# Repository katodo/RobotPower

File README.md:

# RobotPower
A Rosserial + **Arduino DUE** based work for Robot's battery and power managment

##Clone and install from source Rosserial 
See reference documentation of [Rosserial](http://wiki.ros.org/rosserial_arduino/Tutorials/Arduino%20IDE%20Setup)

##Add u8glib library to Arduino's GUI
(u8glib)[https://github.com/olikraus/u8glib] library is needed, you can add (Arduino ZIP version)[https://github.com/olikraus/U8glib_Arduino/releases/latest] directly from **Arduino GUI -> Sketch -> Include Library -> Add .ZIP Library**

##Clone this code and load it in an Arduino DUE board.

##Run RosCore.

```
you$ roscore
... logging to /home/you/.ros/log/d6f526e8-644b-11e6-8eba-00044b26fb48/roslaunch-plutarco-3242.log
Checking log directory for disk usage. This may take awhile.
Press Ctrl-C to interrupt
Done checking log file disk usage. Usage is <1GB.

started roslaunch server http://plutarco.local:56239/
ros_comm version 1.11.20

SUMMARY
========

PARAMETERS
 * /rosdistro: indigo
 * /rosversion: 1.11.20

NODES

auto-starting new master
process[master]: started with pid [3253]
ROS_MASTER_URI=http://plutarco.local:11311/

setting /run_id to d6f526e8-644b-11e6-8eba-00044b26fb48
process[rosout-1]: started with pid [3266]
started core service [/rosout]
```
pay attention to ROS version: *rosdistro: indigo* 

##Run serial_node.py 
This is an output example of output of my *rosrun rosserial_python serial_node.py /dev/ttyACM0* command
```
you$ rosrun rosserial_python serial_node.py /dev/ttyACM0
[INFO] [WallTime: 1471330769.673572] ROS Serial Python Node
[INFO] [WallTime: 1471330769.679982] Connecting to /dev/ttyACM0 at 57600 baud
[ERROR] [WallTime: 1471330786.785870] Unable to sync with device; possible link problem or link software version mismatch such as hydro rosserial_python with groovy Arduino
[INFO] [WallTime: 1471330786.966402] Note: publish buffer size is 512 bytes
[INFO] [WallTime: 1471330786.966842] Setup publisher on BatteryState [sensor_msgs/BatteryState]
[INFO] [WallTime: 1471330786.971024] Setup publisher on adc [rosserial_arduino/Adc]
[INFO] [WallTime: 1471330786.975058] Setup publisher on chatter [std_msgs/String]
```

#Usage Example
There is 3 type of published messages in the first ( test ) release of this code
```
you$ rostopic list 
/BatteryState
/adc
/chatter
```

In a console I can see published message content with *rostopic echo* command

### Chatter message
```
you$ rostopic echo /chatter 
data: hello world!
---
data: hello world!
---
```

### ADC message
```
your$ rostopic echo /adc     
adc0: 0
adc1: 0
adc2: 0
adc3: 0
adc4: 0
adc5: 46509
```

### BatteryState message
```
you$ rostopic echo /BatteryState 
header: 
  seq: 996
  stamp: 
    secs: 0
    nsecs:         0
  frame_id: ''
voltage: 23.2210006714
current: -2.90000009537
charge: 0.240999996662
capacity: 3.59999990463
design_capacity: 5.0
percentage: 0.930000007153
power_supply_status: 2
power_supply_health: 1
power_supply_technology: 2
present: True
cell_voltage: [3.628000020980835, 3.628999948501587, 3.515000104904175, 4.0]
location: robot
serial_number: 123456790
---

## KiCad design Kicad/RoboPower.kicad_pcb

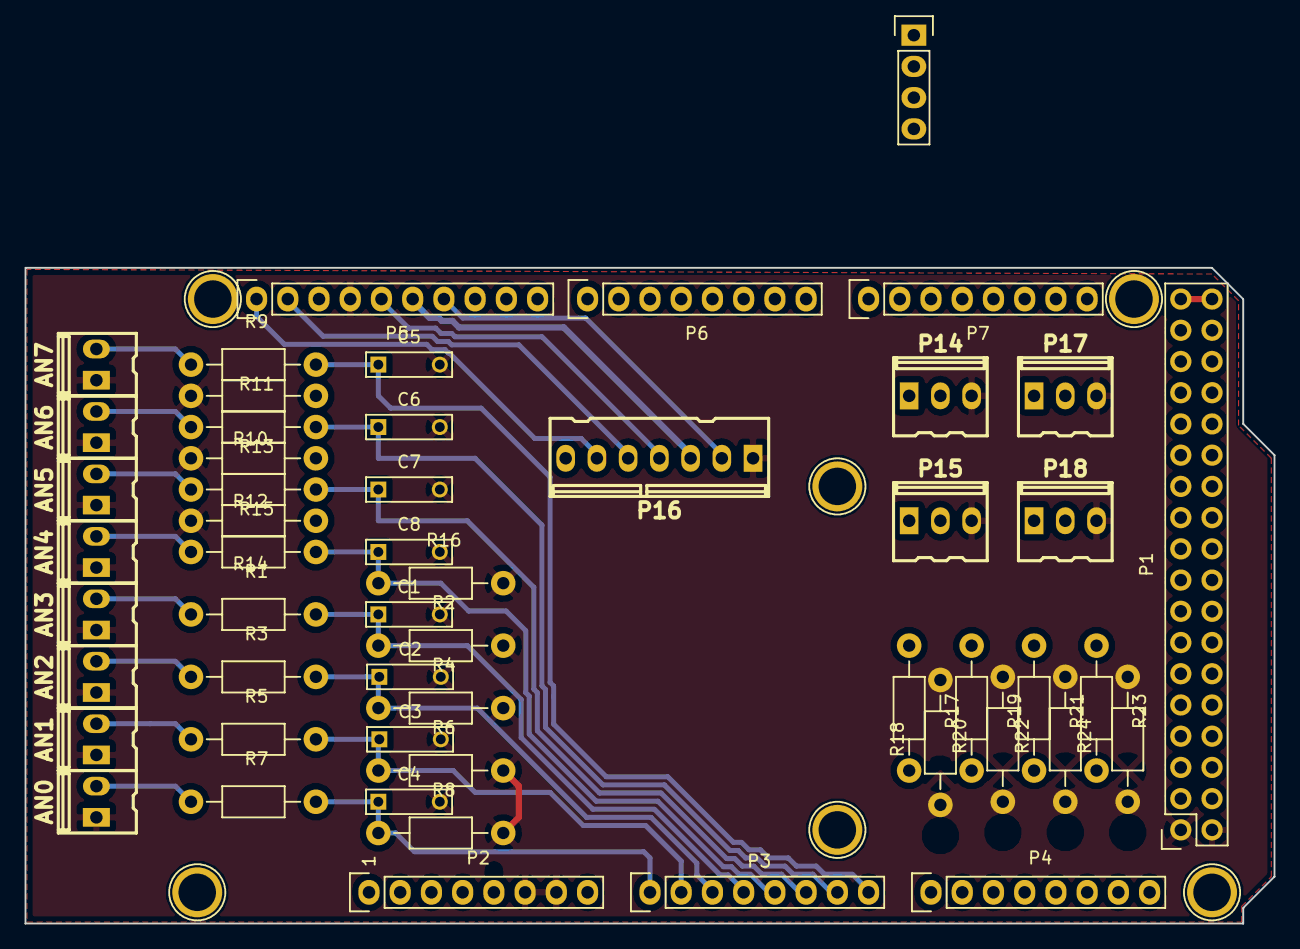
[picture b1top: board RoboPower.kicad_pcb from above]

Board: 2 copper layers, 101.6 x 53.3 mm, 59 parts (0 on the bottom side), 34 nets.

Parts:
AN0, AN1, AN2, AN3, AN4, AN5, AN6, AN7: CONN_01X02; kk100_22-23-2021
C1, C2, C3, C4, C5, C6, C7, C8: 100nF; C_Rect_L7_W2_P5
P1: Digital; Socket_Strip_Arduino_2x18
P2: Power; Socket_Strip_Arduino_1x08
P3, P4: Analog; Socket_Strip_Arduino_1x08
P5: PWM; Socket_Strip_Arduino_1x10
P6: PWM; Socket_Strip_Arduino_1x08
P7: Communication; Socket_Strip_Arduino_1x08
P8, P9, P10, P11, P12, P13: CONN_01X01; Arduino_1pin
P14, P15, P17, P18: CONN_01X03; kk100_22-23-2031
P16: CONN_01X07; kk100_22-23-2071
P19: CONN_01X04; Pin_Header_Straight_1x04
R1, R3, R5, R7: 150K; Resistor_Horizontal_RM10mm
R2, R4, R6, R8, R10, R12, R14, R16, R18, R20, R22, R24: 12K; Resistor_Horizontal_RM10mm
R9, R11: 47K0; Resistor_Horizontal_RM10mm
R13, R15: 150K0; Resistor_Horizontal_RM10mm
R17, R19, R21, R23: 6K8; Resistor_Horizontal_RM10mm

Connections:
+3V3: P2.4, P16.7, P19.2
+5V: P1.35, P1.36, P2.5, P14.3, P15.3, P17.3, P18.3
ACP: P5.6, P16.3
AN0: C4.1, P3.1, R7.2, R8.1
AN1: C3.1, P3.2, R5.2, R6.1
AN2: C2.1, P3.3, R3.2, R4.1
AN3: C1.1, P3.4, R1.2, R2.1
AN4: C8.1, P3.5, R15.2, R16.1
AN5: C7.1, P3.6, R13.2, R14.1
AN6: C6.1, P3.7, R11.2, R12.1
AN7: C5.1, P3.8, R9.2, R10.1
AN8: P4.1, R17.2, R18.1
AN9: P4.2, R19.2, R20.1
AN10: P4.3, R21.2, R22.1
AN11: P4.4, R23.2, R24.1
CHGEN: P5.5, P16.4
GND: AN0.1, AN1.1, AN2.1, AN3.1, AN4.1, AN5.1, AN6.1, AN7.1, C1.2, C2.2, C3.2, C4.2, C5.2, C6.2, C7.2, C8.2, P1.1, P1.2, P2.6, P2.7, P5.4, P14.1, P15.1, P16.1, P17.1, P18.1, P19.1, R2.2, R4.2, R6.2, R8.2, R10.2, R12.2, R14.2, R16.2, R18.2, R20.2, R22.2, R24.2
IN0: AN0.2, R7.1
IN1: AN1.2, R5.1
IN2: AN2.2, R3.1
IN3: AN3.2, R1.1
IN4: AN4.2, R15.1
IN5: AN5.2, R13.1
IN6: AN6.2, R11.1
IN7: AN7.2, R9.1
unnamed: P14.2, R17.1
unnamed: P15.2, R19.1
unnamed: P17.2, R21.1
unnamed: P18.2, R23.1
SCL: P7.8, P19.3
SCL1: P5.1, P16.6
SDA: P7.7, P19.4
SDA1: P5.2, P16.5
SMBALERT: P5.7, P16.2

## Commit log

2016-08-16 Initial release of rosserial based code with 3 type of differente message published.
2016-08-16 Update README.md
    added a small usage example of first committed code
2016-08-16 Kicad Scheme
    first release of scheme and PCB
2016-08-16 Work In Progress
    Varius improvment
2016-08-17 Introduced analog's data view on LCD
2016-08-17 Readme Update
    Readme Update
2016-08-17 work in progress
2016-10-23 Screen rotation... a first compilation test after some mounth of vacation :)
